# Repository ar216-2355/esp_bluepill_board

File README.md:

万能基板

主目的
- ESP-WROOM-02 を乗せてパソコンとbluepillとのwi-fi通信を実現

できること
- DCモーター　６台　駆動
- 電磁弁　４台　駆動
- ステッピングモーター　１台　駆動
- NeoPixel　１台（使えるか未確認）　駆動
- CAN通信可能
- PA10をHIGHにすることでUSB通信可能

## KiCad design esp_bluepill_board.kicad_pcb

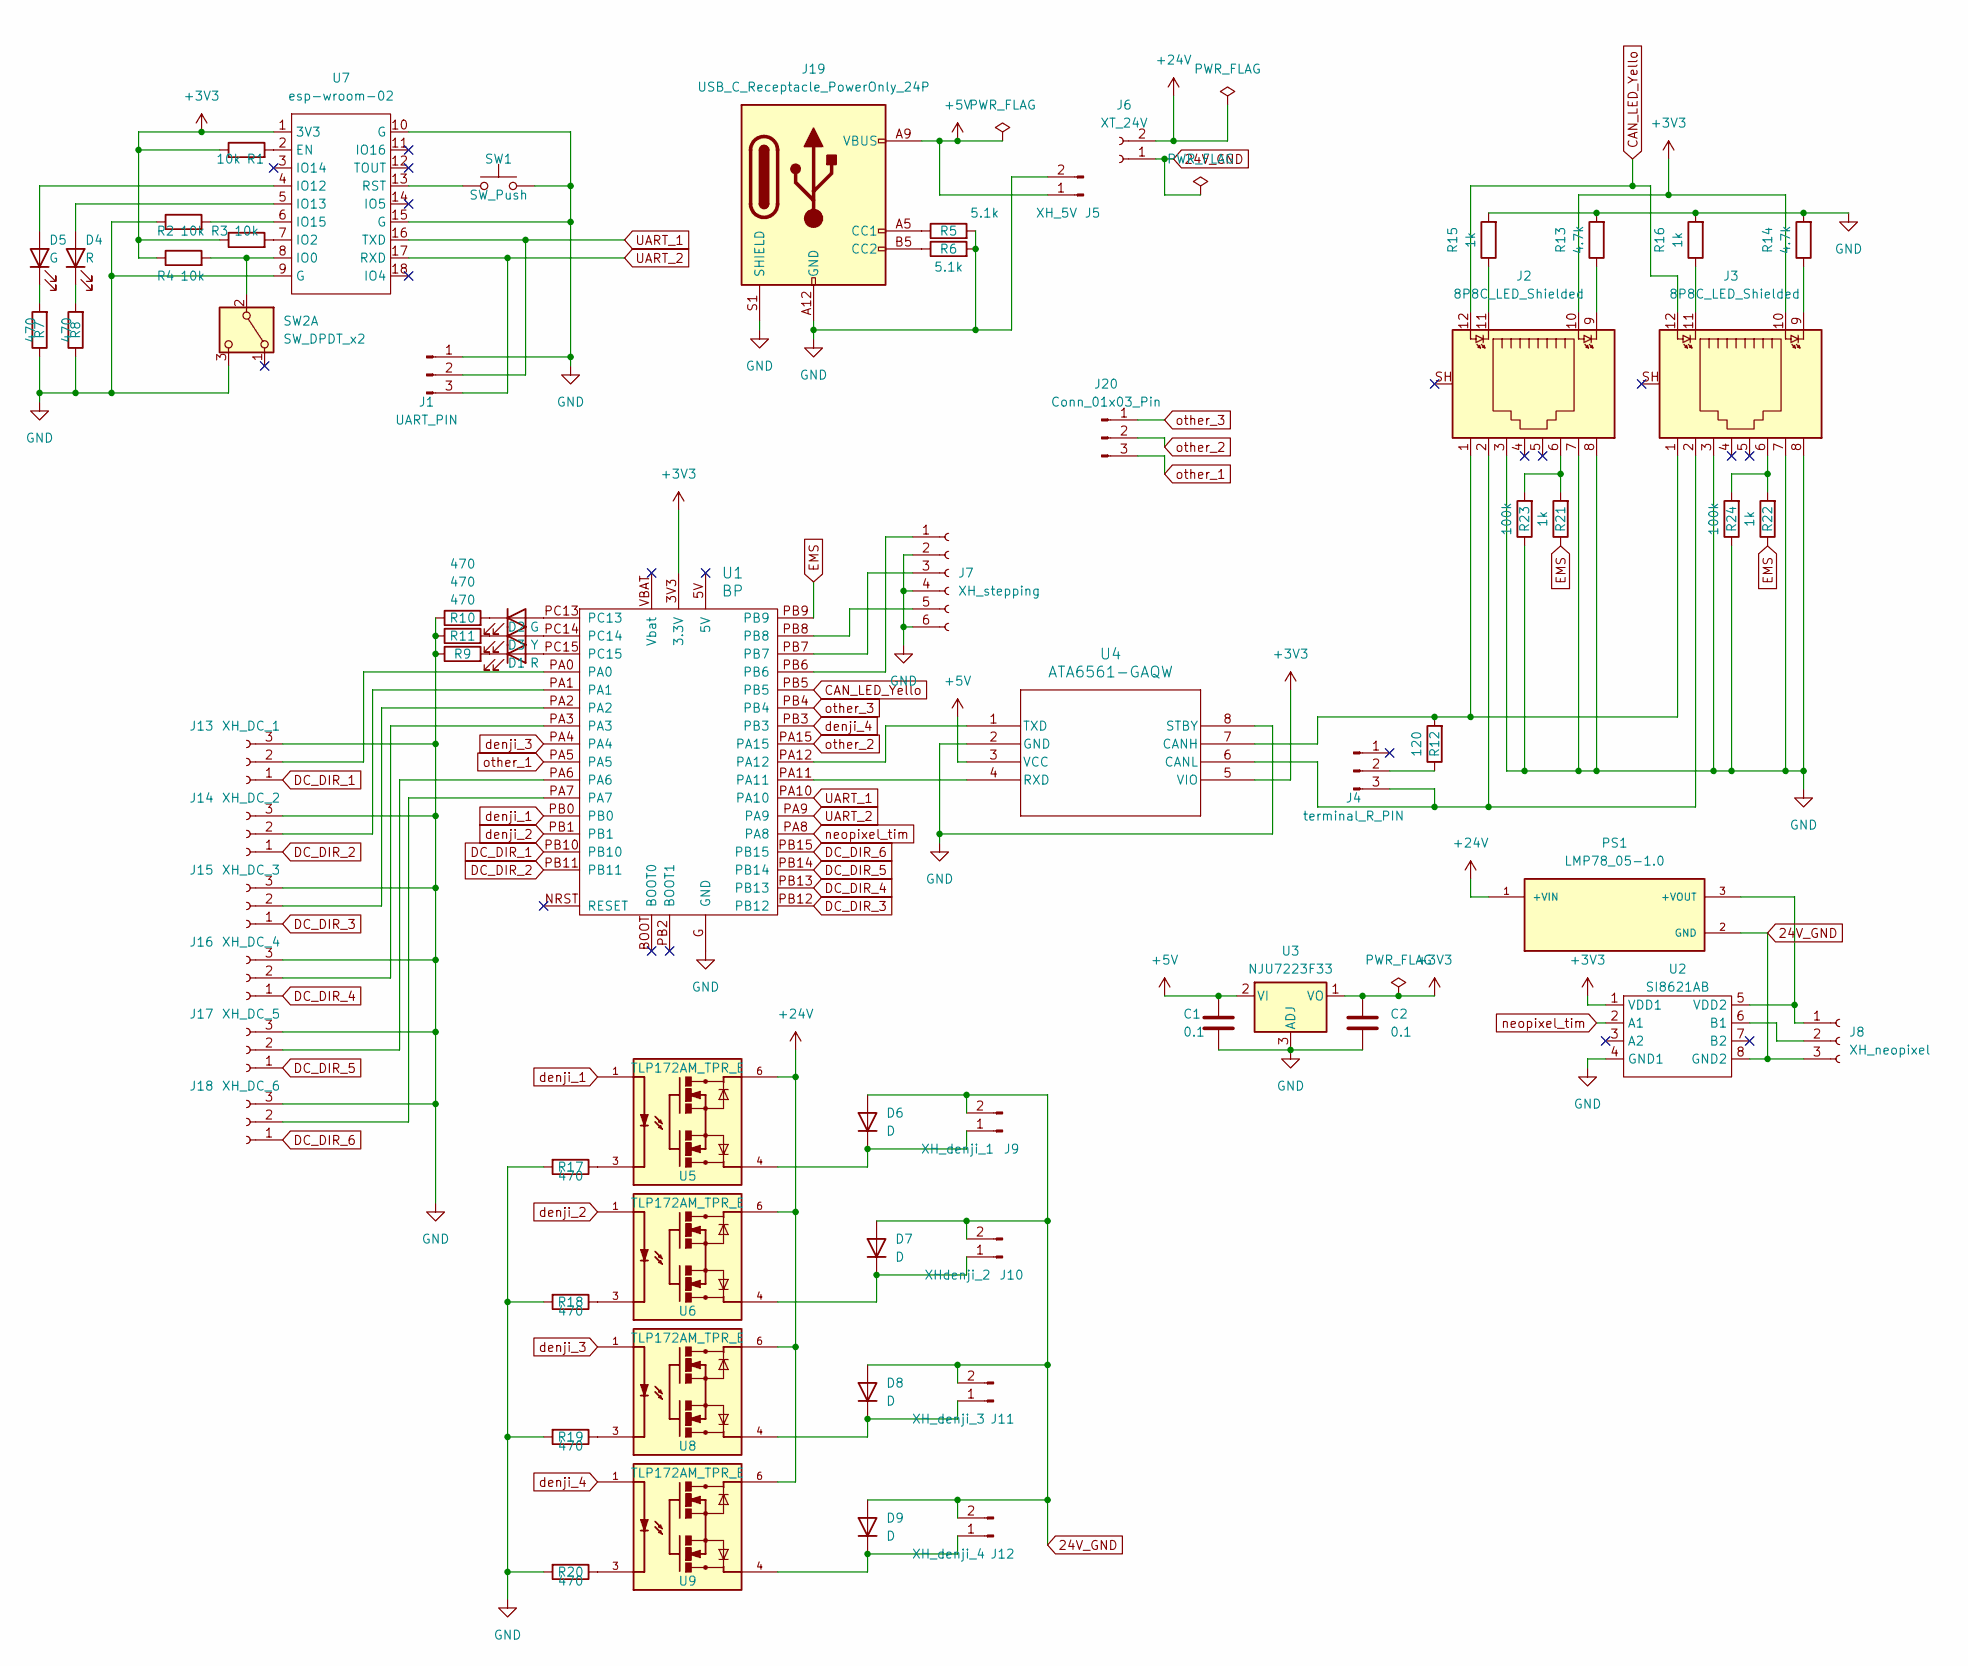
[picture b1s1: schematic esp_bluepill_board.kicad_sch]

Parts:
C1, C2: 0.1; C_0805_2012Metric
D1, D4: R; LED_0805_2012Metric
D2, D5: G; LED_0805_2012Metric
D3: Y; LED_0805_2012Metric
D6, D7, D8, D9: D; SOD-123FL
J1: UART_PIN; PinHeader_1x03_P2.54mm_Vertical
J2, J3: 8P8C_LED_Shielded; RJHSE-5381 LAN_port
J4: terminal_R_PIN; PinHeader_1x03_P2.54mm_Vertical
J5: XH_5V; JST_XH_B2B-XH-A_1x02_P2.50mm_Vertical
J6: XT_24V; AMASS_XT30U-F_1x02_P5.0mm_Vertical
J7: XH_stepping; JST_XH_B6B-XH-A_1x06_P2.50mm_Vertical
J8: XH_neopixel; JST_XH_B3B-XH-A_1x03_P2.50mm_Vertical
J9: XH_denji_1; JST_XH_B2B-XH-A_1x02_P2.50mm_Vertical
J10: XHdenji_2; JST_XH_B2B-XH-A_1x02_P2.50mm_Vertical
J11: XH_denji_3; JST_XH_B2B-XH-A_1x02_P2.50mm_Vertical
J12: XH_denji_4; JST_XH_B2B-XH-A_1x02_P2.50mm_Vertical
J13: XH_DC_1; JST_XH_B3B-XH-A_1x03_P2.50mm_Vertical
J14: XH_DC_2; JST_XH_B3B-XH-A_1x03_P2.50mm_Vertical
J15: XH_DC_3; JST_XH_B3B-XH-A_1x03_P2.50mm_Vertical
J16: XH_DC_4; JST_XH_B3B-XH-A_1x03_P2.50mm_Vertical
J17: XH_DC_5; JST_XH_B3B-XH-A_1x03_P2.50mm_Vertical
J18: XH_DC_6; JST_XH_B3B-XH-A_1x03_P2.50mm_Vertical
J19: USB_C_Receptacle_PowerOnly_24P; USB_C_Receptacle_G-Switch_GT-USB-7010ASV
J20: Conn_01x03_Pin; PinHeader_1x03_P2.54mm_Vertical
PS1: LMP78_05-1.0; CONV_LMP78_05-1.0; PARTREV 2022-1.9
R1, R2, R3, R4: 10k; R_0402_1005Metric
R5, R6: 5.1k; R_0402_1005Metric
R7, R8, R9, R10, R11, R17, R18, R19, R20: 470; R_0402_1005Metric
R12: 120; R_0402_1005Metric
R13, R14: 4.7k; R_0402_1005Metric
R15, R16, R21, R22: 1k; R_0402_1005Metric
R23, R24: 100k; R_0402_1005Metric
SW1: SW_Push; TS-1088-AR02016
SW2: SW_DPDT_x2; PinHeader_1x03_P2.54mm_Vertical
U1: BP; blue_pill
U2: SI8621AB
U3: NJU7223F33; TO-220-3_Vertical
U4: ATA6561-GAQW; SOIC8_4P9X3P9MC_MCH-M
U5, U6, U8, U9: TLP172AM_TPR_E; SOIC254P700X220-4N; PARTREV 5.0
U7: esp-wroom-02

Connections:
24V_GND: D6.2 (A), D7.2 (A), D8.2 (A), D9.2 (A), J6.1, J8.3, J9.2, J10.2, J11.2, J12.2, PS1.2 (GND), U2.8 (GND2)
+3V3: C2.1, J2.10, J3.10, R1.1, R3.1, R4.1, U1.3V3 (3.3V), U2.1 (VDD1), U3.1 (VO), U4.5 (VIO), U7.1 (3V3)
+5V: C1.1, J5.1, J19.A4 (VBUS), J19.A9 (VBUS), J19.B4 (VBUS), J19.B9 (VBUS), U3.2 (VI), U4.3 (VCC)
+24V: J6.2, PS1.1 (+VIN), U5.6, U6.6, U8.6, U9.6
CAN_LED_Yello: J2.12, J3.12, U1.PB5
DC_DIR_1: J13.1, U1.PB10
DC_DIR_2: J14.1, U1.PB11
DC_DIR_3: J15.1, U1.PB12
DC_DIR_4: J16.1, U1.PB13
DC_DIR_5: J17.1, U1.PB14
DC_DIR_6: J18.1, U1.PB15
EMS: R21.1, R22.1, U1.PB9
GND: C1.2, C2.2, J1.1, J2.3, J2.7, J2.8, J2.SH, J3.3, J3.7, J3.8, J3.SH, J5.2, J7.2, J7.4, J7.6, J13.3, J14.3, J15.3, J16.3, J17.3, J18.3, J19.A1 (GND), J19.A12 (GND), J19.B1 (GND), J19.B12 (GND), J19.S1 (SHIELD), R2.1, R5.2, R6.2, R7.1, R8.1, R9.1, R10.1, R11.1, R13.2, R14.2, R15.2, R16.2, R17.2, R18.2, R19.2, R20.2, R23.1, R24.1, SW1.2, SW2.3 (C), U1.G (GND), U2.4 (GND1), U3.3 (ADJ), U4.2 (GND), U4.8 (STBY), U7.9 (G), U7.10 (G), U7.15 (G)
unnamed: D1.2 (A), U1.PC15
unnamed: D1.1 (K), R9.2
unnamed: D2.2 (A), U1.PC13
unnamed: D2.1 (K), R10.2
unnamed: D3.2 (A), U1.PC14
unnamed: D3.1 (K), R11.2
unnamed: D4.2 (A), U7.5 (IO13)
unnamed: D4.1 (K), R8.2
unnamed: D5.2 (A), U7.4 (IO12)
unnamed: D5.1 (K), R7.2
unnamed: D6.1 (K), J9.1, U5.4
unnamed: D7.1 (K), J10.1, U6.4
unnamed: D8.1 (K), J11.1, U8.4
unnamed: D9.1 (K), J12.1, U9.4
unnamed: J2.6, R21.2, R23.2
unnamed: J2.9, R13.1
unnamed: J2.11, R15.1
unnamed: J3.6, R22.2, R24.2
unnamed: J3.9, R14.1
unnamed: J3.11, R16.1
unnamed: J4.2, R12.1
unnamed: J2.2, J3.2, J4.3, U4.6 (CANL)
unnamed: J7.1, U1.PB6
unnamed: J7.3, U1.PB7
unnamed: J7.5, U1.PB8
unnamed: J8.1, PS1.3 (+VOUT), U2.5 (VDD2)
unnamed: J8.2, U2.6 (B1)
unnamed: J13.2, U1.PA0
unnamed: J14.2, U1.PA1
unnamed: J15.2, U1.PA2
unnamed: J16.2, U1.PA3
unnamed: J17.2, U1.PA6
unnamed: J18.2, U1.PA7
unnamed: J19.A5 (CC1), R5.1
unnamed: J19.B5 (CC2), R6.1
unnamed: R17.1, U5.3
unnamed: R18.1, U6.3
unnamed: R19.1, U8.3
unnamed: R20.1, U9.3
unnamed: R4.2, SW2.2 (B), U7.8 (IO0)
unnamed: J2.1, J3.1, R12.2, U4.7 (CANH)
unnamed: U1.PA11, U4.4 (RXD)
unnamed: U1.PA12, U4.1 (TXD)
unnamed: R1.2, U7.2 (EN)
unnamed: R3.2, U7.7 (IO2)
unnamed: R2.2, U7.6 (IO15)
unnamed: SW1.1, U7.13 (RST)
UART_1: J1.2, U1.PA10, U7.16 (TXD)
UART_2: J1.3, U1.PA9, U7.17 (RXD)
denji_1: U1.PB0, U5.1
denji_2: U1.PB1, U6.1
denji_3: U1.PA4, U8.1
denji_4: U1.PB3, U9.1
neopixel_tim: U1.PA8, U2.2 (A1)
other_1: J20.3, U1.PA5
other_2: J20.2, U1.PA15
other_3: J20.1, U1.PB4

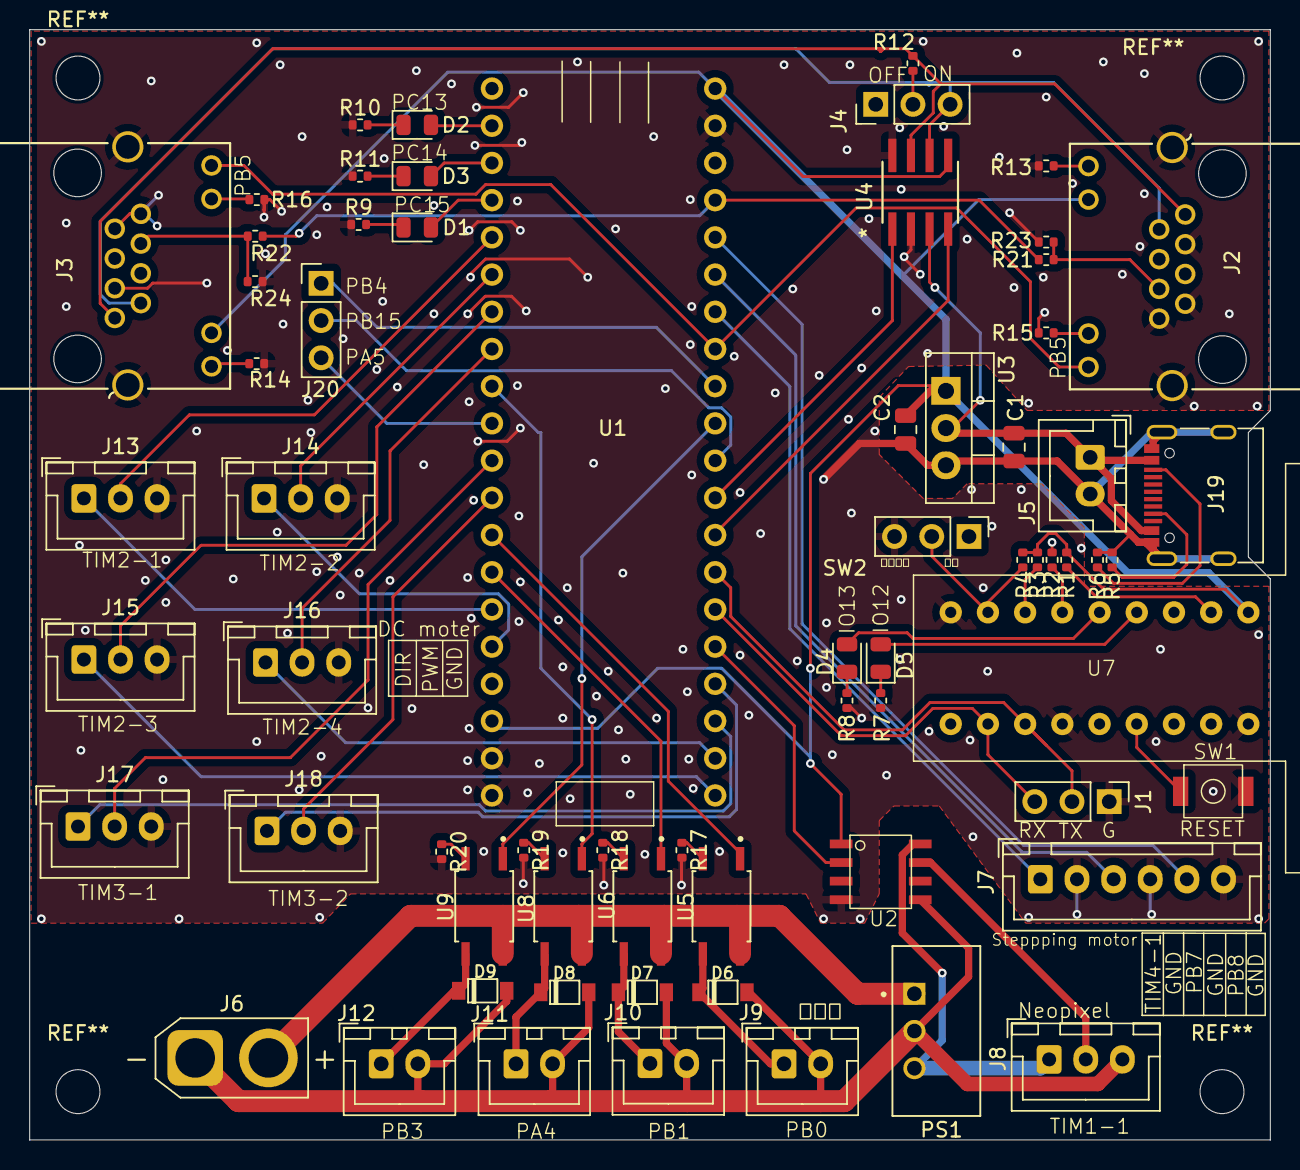
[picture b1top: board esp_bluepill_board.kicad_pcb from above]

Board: 2 copper layers, 84.7 x 75.8 mm, 67 parts (0 on the bottom side), 70 nets.

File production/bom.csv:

Designator,Footprint,Quantity,Value,LCSC Part #
"C1, C2",0805,2,0.1,
"D1, D4",0805,2,R,
"D2, D5",0805,2,G,
D3,0805,1,Y,
"D6, D7, D8, D9",SOD-123FL,4,D,
J1,PinHeader_1x03_P2.54mm_Vertical,1,UART_PIN,
J10,JST_XH_B2B-XH-A_1x02_P2.50mm_Vertical,1,XHdenji_2,
J11,JST_XH_B2B-XH-A_1x02_P2.50mm_Vertical,1,XH_denji_3,
J12,JST_XH_B2B-XH-A_1x02_P2.50mm_Vertical,1,XH_denji_4,
J13,JST_XH_B3B-XH-A_1x03_P2.50mm_Vertical,1,XH_DC_1,
J14,JST_XH_B3B-XH-A_1x03_P2.50mm_Vertical,1,XH_DC_2,
J15,JST_XH_B3B-XH-A_1x03_P2.50mm_Vertical,1,XH_DC_3,
J16,JST_XH_B3B-XH-A_1x03_P2.50mm_Vertical,1,XH_DC_4,
J17,JST_XH_B3B-XH-A_1x03_P2.50mm_Vertical,1,XH_DC_5,
J18,JST_XH_B3B-XH-A_1x03_P2.50mm_Vertical,1,XH_DC_6,
J19,USB_C_Receptacle_G-Switch_GT-USB-7010ASV,1,USB_C_Receptacle_PowerOnly_24P,
"J2, J3",RJHSE-5381 LAN_port,2,8P8C_LED_Shielded,
J20,PinHeader_1x03_P2.54mm_Vertical,1,Conn_01x03_Pin,
J4,PinHeader_1x03_P2.54mm_Vertical,1,terminal_R_PIN,
J5,JST_XH_B2B-XH-A_1x02_P2.50mm_Vertical,1,XH_5V,
J6,AMASS_XT30U-F_1x02_P5.0mm_Vertical,1,XT_24V,
J7,JST_XH_B6B-XH-A_1x06_P2.50mm_Vertical,1,XH_stepping,
J8,JST_XH_B3B-XH-A_1x03_P2.50mm_Vertical,1,XH_neopixel,
J9,JST_XH_B2B-XH-A_1x02_P2.50mm_Vertical,1,XH_denji_1,
PS1,CONV_LMP78_05-1.0,1,LMP78_05-1.0,
"R1, R2, R3, R4",0402,4,10k,
"R10, R11, R17, R18, R19, R20, R7, R8, R9",0402,9,470,
R12,0402,1,120,
"R13, R14",0402,2,4.7k,
"R15, R16, R21, R22",0402,4,1k,
"R23, R24",0402,2,100k,
"R5, R6",0402,2,5.1k,
SW1,TS-1088-AR02016,1,SW_Push,
SW2,PinHeader_1x03_P2.54mm_Vertical,1,SW_DPDT_x2,
U1,blue_pill,1,BP,
U2,SI8621AB,1,SI8621AB,
U3,TO-220-3_Vertical,1,NJU7223F33,
U4,SOIC8_4P9X3P9MC_MCH-M,1,ATA6561-GAQW,
"U5, U6, U8, U9",SOIC254P700X220-4N,4,TLP172AM_TPR_E,
U7,esp-wroom-02,1,esp-wroom-02,

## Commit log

2026-01-07 readme
2026-01-07 readme2
2026-01-08 rewqrewq

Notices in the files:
parts and their libraries:
Copyright 2016 Accelerated Designs. All rights reserved.
